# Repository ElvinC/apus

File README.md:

# The Apus Flight Computer (Work in progress and untested!)

Just a smol board for rockets.

Basically the [rocketbeacon](https://github.com/ElvinC/rocketbeacon) with added deployment channels and sensors.

Rev. 1.0 has the following hardware:

* STM32WLE5 MCU Built-in sub-GHz transceiver (for telemetry or RDF) tuned for the 440MHz band
* 2x pyro deployment channels with continuity detection
* 16Mbit flash (W25Q16JVUXIQ)
* BMI270 IMU
* MS5607 Barometer
* Reverse voltage protection
* 13x36mm board size with 2x M2 mounting holes

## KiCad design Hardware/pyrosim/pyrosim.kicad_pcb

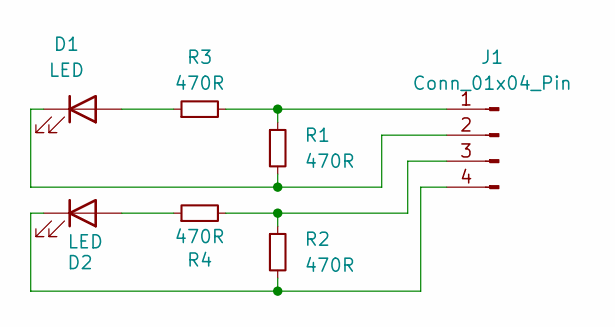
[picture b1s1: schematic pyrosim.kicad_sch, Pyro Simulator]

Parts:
D1, D2: LED; LED_0603_1608Metric
J1: Conn_01x04_Pin; PinHeader_1x04_P2.54mm_Horizontal
R1, R2, R3, R4: 470R; R_0603_1608Metric

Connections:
unnamed: D1.2 (A), R3.1
unnamed: D1.1 (K), J1.2, R1.2
unnamed: D2.2 (A), R4.1
unnamed: D2.1 (K), J1.4, R2.2
unnamed: J1.1, R1.1, R3.2
unnamed: J1.3, R2.1, R4.2

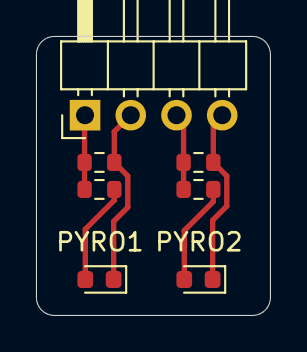
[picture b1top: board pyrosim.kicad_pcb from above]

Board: 2 copper layers, 13.0 x 15.5 mm, 7 parts (0 on the bottom side), 6 nets.

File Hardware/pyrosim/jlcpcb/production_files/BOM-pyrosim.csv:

Comment,Designator,Footprint,LCSC,Quantity
470R,R4,R_0603_1608Metric,,1
Conn_01x04_Pin,J1,PinHeader_1x04_P2.54mm_Horizontal,,1
470R,R3,R_0603_1608Metric,,1
LED,D1,LED_0603_1608Metric,,1
470R,R2,R_0603_1608Metric,,1
470R,R1,R_0603_1608Metric,,1
LED,D2,LED_0603_1608Metric,,1

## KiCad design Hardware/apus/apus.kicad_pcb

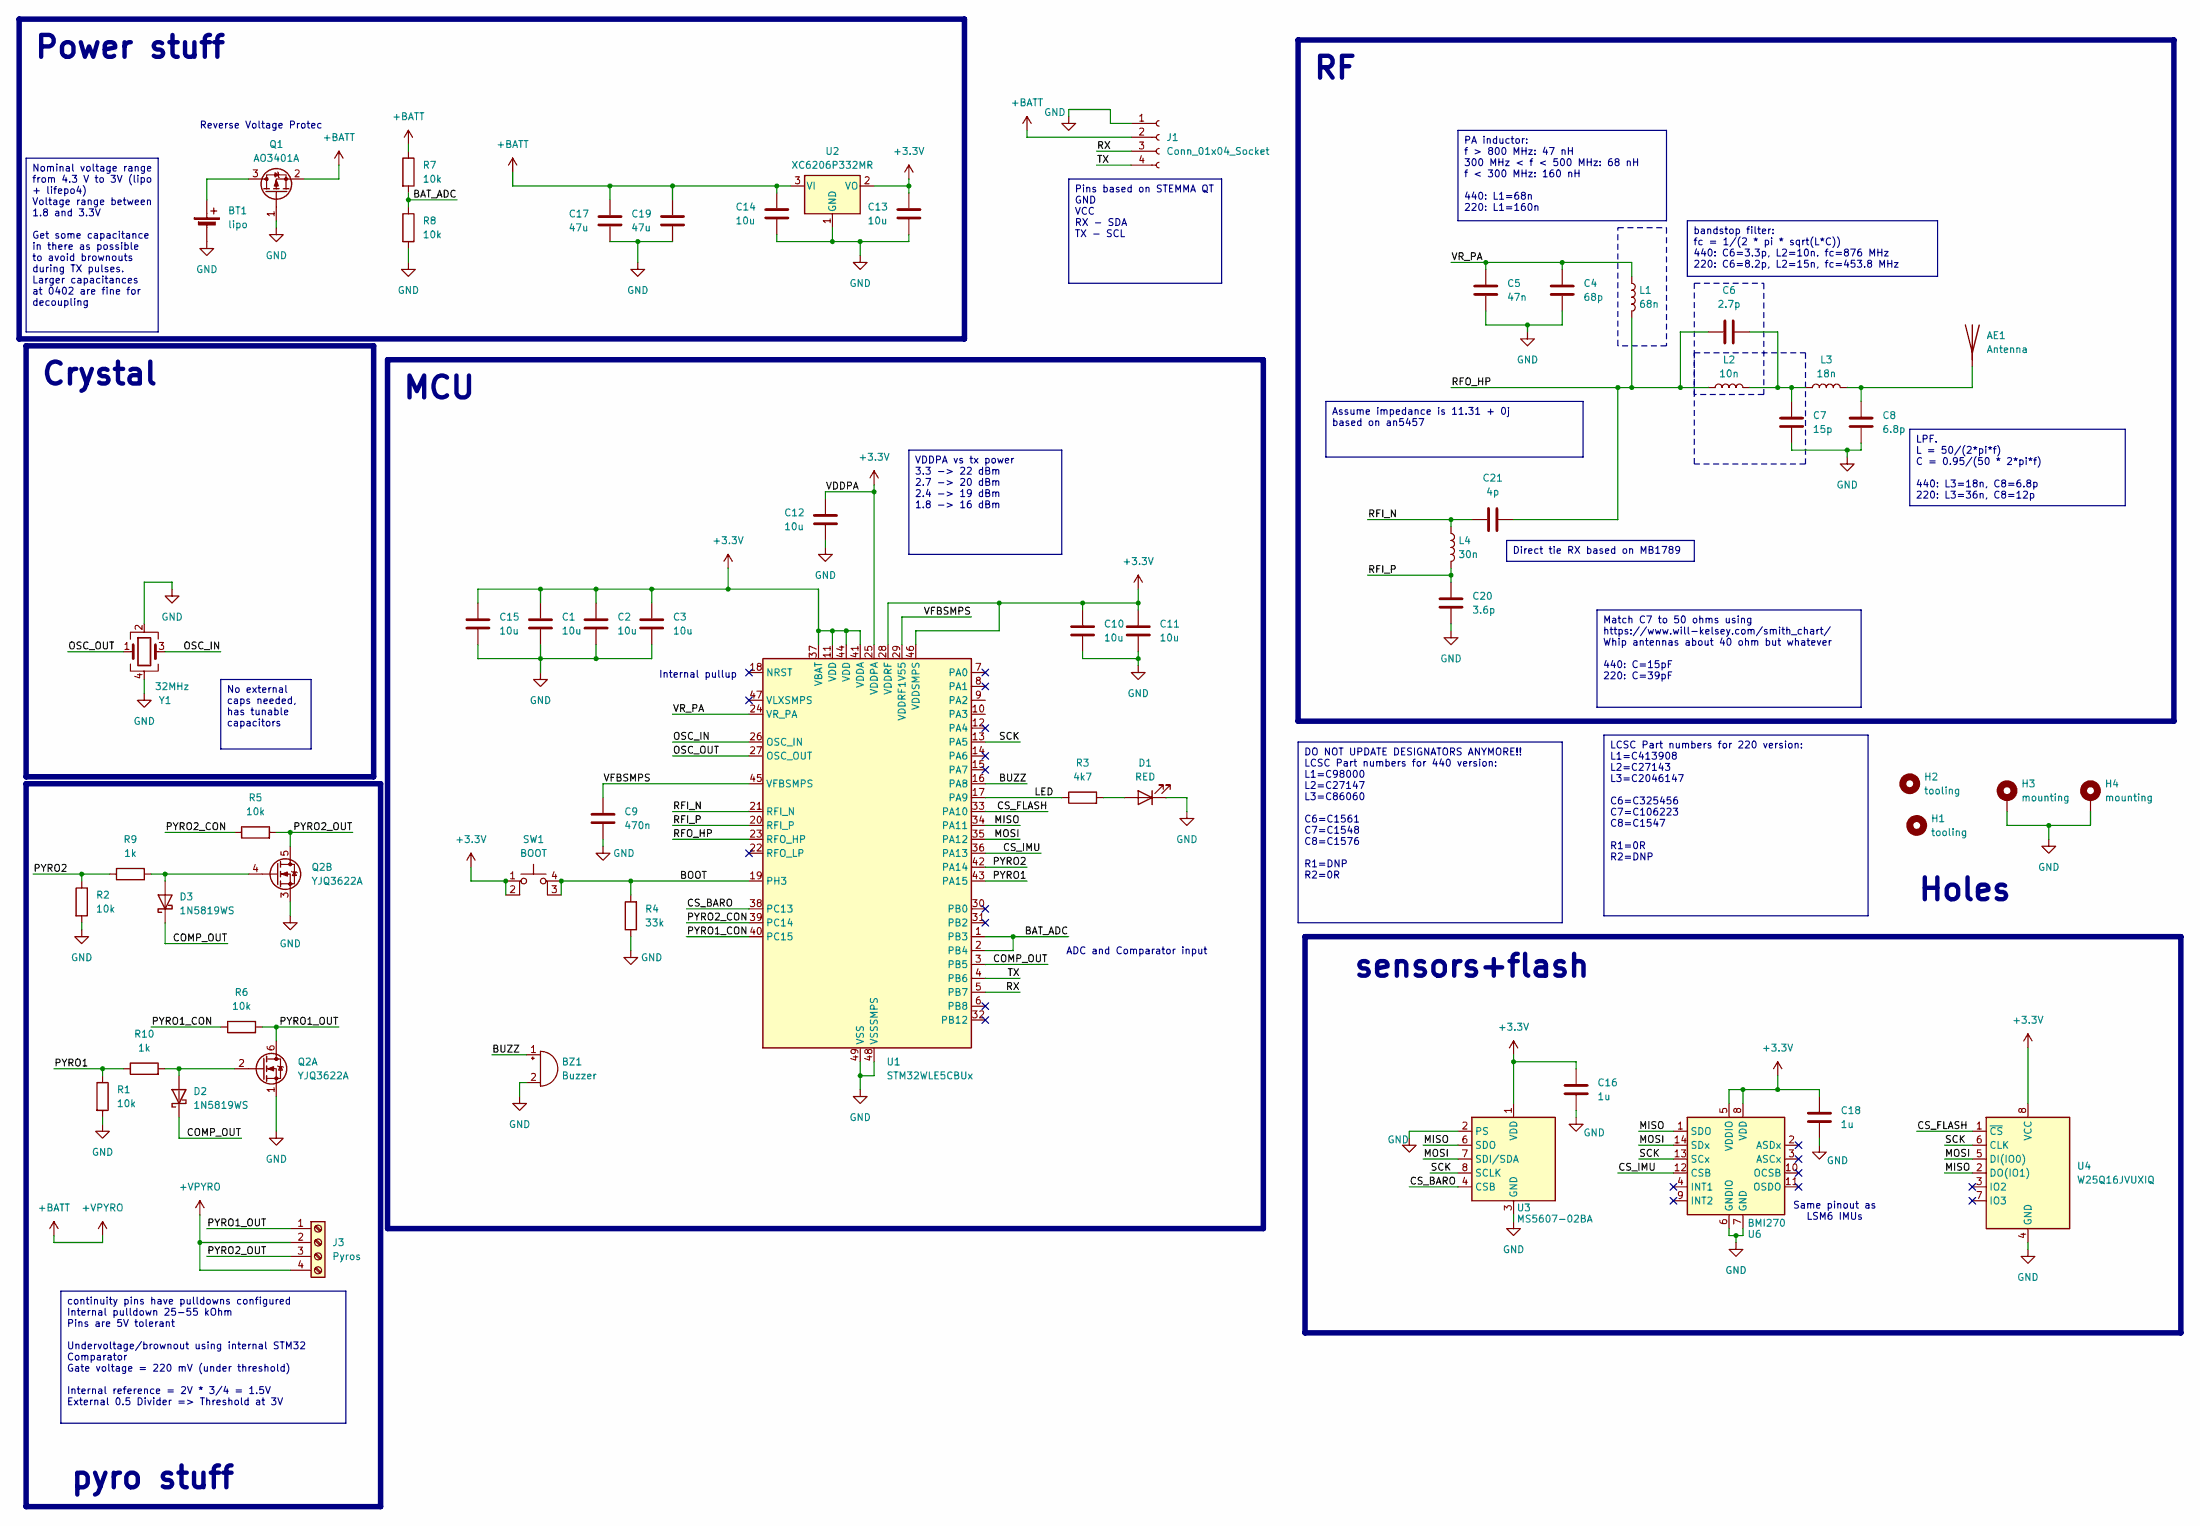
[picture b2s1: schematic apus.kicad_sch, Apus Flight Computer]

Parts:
AE1: Antenna; whip_antenna
BT1: lipo; TerminalBlock_TE_282834-2_1x02_P2.54mm_Horizontal
BZ1: Buzzer; Buzzer_Murata_PKMCS0909E; LCSC C96127
C1, C2, C3, C10, C11, C12, C13, C14, C15: 10u; C_0402_1005Metric
C4: 68p; C_0402_1005Metric
C5: 47n; C_0402_1005Metric
C6: 2.7p; C_0402_1005Metric
C7: 15p; C_0402_1005Metric
C8: 6.8p; C_0402_1005Metric
C9: 470n; C_0402_1005Metric
C16, C18: 1u; C_0402_1005Metric
C17, C19: 47u; C_0805_2012Metric; LCSC C16780
C20: 3.6p; C_0402_1005Metric
C21: 4p; C_0402_1005Metric
D1: RED; LED_0603_1608Metric
D2, D3: 1N5819WS; D_SOD-323
H1, H2: tooling; toolinghole
H3, H4: mounting; MountingHole_2.2mm_M2_DIN965_Pad
J1: Conn_01x04_Socket; JST_SH_SM04B-SRSS-TB_1x04-1MP_P1.00mm_Horizontal; LCSC C160404
J3: Pyros; TerminalBlock_Phoenix_MPT-0,5-4-2.54_1x04_P2.54mm_Horizontal; LCSC C918122
L1: 68n; L_0402_1005Metric
L2: 10n; L_0402_1005Metric
L3: 18n; L_0402_1005Metric
L4: 30n; L_0402_1005Metric
Q1: AO3401A; SOT-23
Q2: YJQ3622A; Vishay_PowerPAK_1212-8_Dual
R1, R2, R5, R6, R7, R8: 10k; R_0402_1005Metric
R3: 4k7; R_0402_1005Metric
R4: 33k; R_0402_1005Metric
R9, R10: 1k; R_0402_1005Metric
SW1: BOOT; SW_1TS026A
U1: STM32WLE5CBUx; QFN-48-1EP_7x7mm_P0.5mm_EP5.6x5.6mm
U2: XC6206P332MR; SOT-23
U3: MS5607-02BA; LGA-8_3x5mm_P1.25mm; LCSC C97627
U4: W25Q16JVUXIQ; Winbond_USON-8-1EP_3x2mm_P0.5mm_EP0.2x1.6mm
U6: BMI270; Bosch_LGA-14_3x2.5mm_P0.5mm
Y1: 32MHz; Crystal_SMD_2016-4Pin_2.0x1.6mm; LCSC C383840

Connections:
+3.3V: C1.1, C2.1, C3.1, C10.1, C11.1, C12.1, C13.1, C15.1, C16.1, C18.1, SW1.1, SW1.2, U1.11 (VDD), U1.25 (VDDPA), U1.28 (VDDRF), U1.37 (VBAT), U1.41 (VDDA), U1.44 (VDD), U1.46 (VDDSMPS), U2.2 (VO), U3.1 (VDD), U4.8 (VCC), U6.5 (VDDIO), U6.8 (VDD)
+BATT: C14.1, C17.1, C19.1, J1.2, J3.2, J3.4, Q1.2 (S), R7.1, U2.3 (VI)
/BAT_ADC: R7.2, R8.1, U1.1 (PB3), U1.2 (PB4)
/BOOT: R4.2, SW1.3 (K), SW1.4 (A), U1.19 (PH3)
/BUZZ: BZ1.1 (+), U1.16 (PA8)
/COMP_OUT: D2.1 (K), D3.1 (K), U1.3 (PB5)
/CS_BARO: U1.38 (PC13), U3.4 (CSB), U3.5 (CSB)
/CS_FLASH: U1.33 (PA10), U4.1 (~CS)
/CS_IMU: U1.36 (PA13), U6.12 (CSB)
/LED: R3.1, U1.17 (PA9)
/MISO: U1.34 (PA11), U3.6 (SDO), U4.2 (DO(IO1)), U6.1 (SDO)
/MOSI: U1.35 (PA12), U3.7 (SDI/SDA), U4.5 (DI(IO0)), U6.14 (SDx)
/OSC_IN: U1.26 (OSC_IN), Y1.3
/OSC_OUT: U1.27 (OSC_OUT), Y1.1
/PYRO1: R1.1, R10.1, U1.43 (PA15)
/PYRO1_CON: R6.1, U1.40 (PC15)
/PYRO1_OUT: J3.1, Q2.6 (D), R6.2
/PYRO2: R2.1, R9.1, U1.42 (PA14)
/PYRO2_CON: R5.1, U1.39 (PC14)
/PYRO2_OUT: J3.3, Q2.5 (D), R5.2
/RFI_N: C21.1, L4.1, U1.21 (RFI_N)
/RFI_P: C20.1, L4.2, U1.20 (RFI_P)
/RFO_HP: C6.1, C21.2, L1.2, L2.1, U1.23 (RFO_HP)
/RX: J1.3, U1.5 (PB7)
/SCK: U1.13 (PA5), U3.8 (SCLK), U4.6 (CLK), U6.13 (SCx)
/TX: J1.4, U1.4 (PB6)
/VFBSMPS: C9.1, U1.29 (VDDRF1V55), U1.45 (VFBSMPS)
/VR_PA: C4.1, C5.1, L1.1, U1.24 (VR_PA)
GND: BT1.2 (-), BZ1.2 (-), C1.2, C2.2, C3.2, C4.2, C5.2, C7.2, C8.2, C9.2, C10.2, C11.2, C12.2, C13.2, C14.2, C15.2, C16.2, C17.2, C18.2, C19.2, C20.2, D1.1 (K), H3.1, H4.1, J1.1, Q1.1 (G), Q2.1 (S), Q2.3 (S), R1.2, R2.2, R4.1, R8.2, U1.48 (VSSSMPS), U1.49 (VSS), U2.1 (GND), U3.2 (PS), U3.3 (GND), U4.4 (GND), U6.6 (GNDIO), U6.7 (GND), Y1.2, Y1.4
unnamed: AE1.1 (A), C8.1, L3.2
unnamed: BT1.1 (+), Q1.3 (D)
unnamed: C6.2, C7.1, L2.2, L3.1
unnamed: D1.2 (A), R3.2
unnamed: D2.2 (A), Q2.2 (G), R10.2
unnamed: D3.2 (A), Q2.4 (G), R9.2

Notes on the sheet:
No external caps needed, has tunable capacitors
Match C7 to 50 ohms using https://www.will-kelsey.com/smith_chart/ Whip antennas about 40 ohm but whatever 440: C=15pF 220: C=39pF
continuity pins have pulldowns configured Internal pulldown 25-55 kOhm Pins are 5V tolerant Undervoltage/brownout using internal STM32 Comparator Gate voltage = 220 mV (under threshold) Internal reference = 2V * 3/4 = 1.5V External 0.5 Divider => Threshold at 3V
PA inductor: f > 800 MHz: 47 nH 300 MHz < f < 500 MHz: 68 nH f < 300 MHz: 160 nH 440: L1=68n 220: L1=160n
bandstop filter: fc = 1/(2 * pi * sqrt(L*C)) 440: C6=3.3p, L2=10n. fc=876 MHz 220: C6=8.2p, L2=15n, fc=453.8 MHz
VDDPA vs tx power 3.3 -> 22 dBm 2.7 -> 20 dBm 2.4 -> 19 dBm 1.8 -> 16 dBm
LCSC Part numbers for 220 version: L1=C413908 L2=C27143 L3=C2046147 C6=C325456 C7=C106223 C8=C1547 R1=0R R2=DNP
Nominal voltage range from 4.3 V to 3V (lipo + lifepo4) Voltage range between 1.8 and 3.3V Get some capacitance in there as possible to avoid brownouts during TX pulses. Larger capacitances at 0402 are fine for decoupling
Direct tie RX based on MB1789
Assume impedance is 11.31 + 0j based on an5457
LPF. L = 50/(2*pi*f) C = 0.95/(50 * 2*pi*f) 440: L3=18n, C8=6.8p 220: L3=36n, C8=12p
Pins based on STEMMA QT GND VCC RX - SDA TX - SCL
DO NOT UPDATE DESIGNATORS ANYMORE!! LCSC Part numbers for 440 version: L1=C98000 L2=C27147 L3=C86060 C6=C1561 C7=C1548 C8=C1576 R1=DNP R2=0R
Holes
Power stuff
MCU
Crystal
sensors+flash
Internal pullup
pyro stuff
Same pinout as LSM6 IMUs
ADC and Comparator input
Reverse Voltage Protec

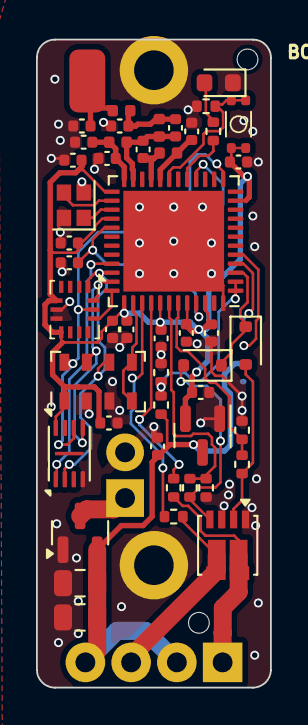
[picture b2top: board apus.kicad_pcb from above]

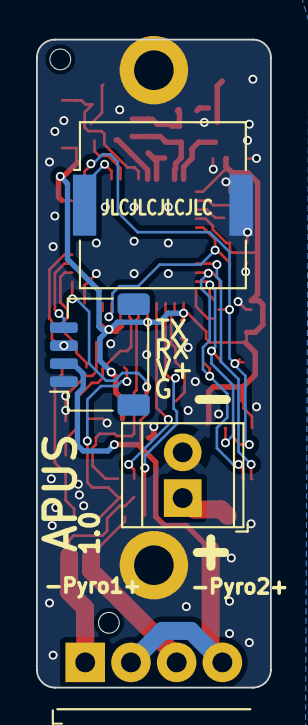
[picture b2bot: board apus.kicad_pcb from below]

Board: 2 copper layers, 13.0 x 36.0 mm, 56 parts (5 on the bottom side), 35 nets.

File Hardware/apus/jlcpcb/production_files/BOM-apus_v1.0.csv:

Comment,Designator,Footprint,LCSC,Quantity
STM32WLE5CBUx,U1,QFN-48-1EP_7x7mm_P0.5mm_EP5.6x5.6mm,C1121847,1
1k,"R10,R9",R_0402_1005Metric,C11702,2
68p,C4,C_0402_1005Metric,C14441,1
100u,"C17,C19",C_0805_2012Metric,C15008,2
AO3401A,Q1,SOT-23,C15127,1
15p,C7,C_0402_1005Metric,C1548,1
10u,"C1,C10,C11,C12,C13,C14,C15,C2,C3",C_0402_1005Metric,C15525,9
2.7p,C6,C_0402_1005Metric,C1561,1
6.8p,C8,C_0402_1005Metric,C1576,1
3.6p,C20,C_0402_1005Metric,C161321,1
1N5819WS,"D2,D3",D_SOD-323,C191023,2
RED,D1,LED_0603_1608Metric,C2286,1
10k,"R1,R2,R5,R6,R7,R8",R_0402_1005Metric,C25744,6
33k,R4,R_0402_1005Metric,C25779,1
4k7,R3,R_0402_1005Metric,C25900,1
10n,L2,L_0402_1005Metric,C27147,1
47n,C5,C_0402_1005Metric,C272875,1
BMI270,U6,Bosch_LGA-14_3x2.5mm_P0.5mm,C2836813,1
W25Q16JVUXIQ,U4,Winbond_USON-8-1EP_3x2mm_P0.5mm_EP0.2x1.6mm,C2843335,1
32MHz,Y1,Crystal_SMD_2016-4Pin_2.0x1.6mm,C383840,1
470n,C9,C_0402_1005Metric,C47339,1
1u,"C16,C18",C_0402_1005Metric,C52923,2
4p,C21,C_0402_1005Metric,C541337,1
XC6206P332MR,U2,SOT-23,C5446,1
18n,L3,L_0402_1005Metric,C86060,1
BOOT,SW1,SW_1TS026A,C913778,1
Pyros,J3,"TerminalBlock_Phoenix_MPT-0,5-4-2.54_1x04_P2.54mm_Horizontal",C918122,1
YJQ3622A,Q2,Vishay_PowerPAK_1212-8_Dual,C919566,1
68n,L1,L_0402_1005Metric,C98000,1
MS5607-02BA,U3,LGA-8_3x5mm_P1.25mm,C9900023641,1
Conn_01x04_Socket,J1,JST_SH_SM04B-SRSS-TB_1x04-1MP_P1.00mm_Horizontal,,1
lipo,BT1,TerminalBlock_TE_282834-2_1x02_P2.54mm_Horizontal,,1
30n,L4,L_0402_1005Metric,,1
Buzzer,BZ1,Buzzer_Murata_PKMCS0909E,,1

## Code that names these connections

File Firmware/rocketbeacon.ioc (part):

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Mcu.Name=STM32WLE5CBUx
Mcu.Package=UFQFPN48
Mcu.UserName=STM32WLE5CBUx
PA10.GPIOParameters=GPIO_Label
PA10.GPIO_Label=CS_FLASH
PA10.Signal=GPIO_Output
PA11.Mode=Full_Duplex_Master
PA11.Signal=SPI1_MISO
PA12.Mode=Full_Duplex_Master
PA12.Signal=SPI1_MOSI
PA13.GPIOParameters=GPIO_Label
PA13.GPIO_Label=CS_IMU
PA13.Signal=GPIO_Output
PA14.GPIOParameters=GPIO_Label
PA14.GPIO_Label=PYRO2
PA14.Signal=GPIO_Output
PA15.GPIOParameters=GPIO_Label
PA15.GPIO_Label=PYRO1
PA15.Signal=GPIO_Output
PA5.Mode=Full_Duplex_Master
PA5.Signal=SPI1_SCK
PA8.Signal=S_TIM1_CH1
PA9.GPIOParameters=GPIO_Label
PA9.GPIO_Label=LED
PA9.Signal=GPIO_Output
PB3.Mode=IN2
PB3.Signal=ADC_IN2
PB4.Mode=INP
PB4.Signal=COMP2_INP
PB5.Mode=ExternalOutput
PB5.Signal=COMP2_OUT
PB6.Mode=Asynchronous
PB6.Signal=USART1_TX
PB7.Mode=Asynchronous
PB7.Signal=USART1_RX
PC13.GPIOParameters=GPIO_Label
PC13.GPIO_Label=CS_BARO
PC13.Signal=GPIO_Output
PC14-OSC32_IN.GPIOParameters=GPIO_Label
PC14-OSC32_IN.GPIO_Label=PYRO2_CON
PC14-OSC32_IN.Signal=GPIO_Input
PC15-OSC32_OUT.GPIOParameters=GPIO_Label
PC15-OSC32_OUT.GPIO_Label=PYRO1_CON
PC15-OSC32_OUT.Signal=GPIO_Input
PH3-BOOT0.GPIOParameters=GPIO_Label
PH3-BOOT0.GPIO_Label=BOOT
PH3-BOOT0.Signal=GPIO_Input
RCC.HSEPRES=2
RCC.HSE_VALUE=32000000
RCC.SYSCLKFreq_VALUE=16000000
RCC.SYSCLKSource=RCC_SYSCLKSOURCE_HSE
board=custom

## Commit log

2025-01-22 Initial commit with 1.0 files
2025-10-17 APRS emulation testing, trying to get long packets working
2025-10-18 Working long packet APRS
2025-10-18 Properly working APRS example
